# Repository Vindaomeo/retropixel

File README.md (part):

# retropixel

RGB matrix on a microcontroller, driven by the PC over USB-CDC with a
lean binary protocol (start token, length, data, CRC-16).

The controller is not just a dumb receiver: after reset it announces itself
once per second with a `READY` token that carries its display geometry.
So the PC doesn't need to know anything about the hardware — it asks.

```
┌──────────────┐      USB-CDC        ┌─────────────────┐   WS2812B
│  PC (Python) │ ◄─────────────────► │  Nano / Pico    │ ──────────► Panel(s)
│  script/     │   MX8 protocol      │  FW/ (FastLED)  │   1…4 data pins
└──────────────┘                     └─────────────────┘
```

Two setups are configured; switching between them takes **one line** in
`FW/mx8_config.h`:

| `MX_BOARD` | Area | Panels | Data pins |
|---|---|---|---|
| `MX_BOARD_8X8` | 8×8 = 64 LEDs | one 8×8 board | D6 |
| `MX_BOARD_16X32` | 32×16 = 512 LEDs | two 8×32 stacked | GP14 and GP17 |

> How a store-bought "8×32" panel is wired internally isn't in any
> datasheet. These ones run **column-wise in a serpentine (zigzag)**: eight pixels
> down the column, the next one back up. `script/mapcheck.py` measures that
> in thirty seconds — a lot faster than guessing.

The host notices none of the difference: it gets the dimensions via `READY` and
sends one contiguous area. How that breaks down into tiles and strands
only the firmware knows.

---

## Behavior after power-on

| State           | Display                      | Serial output        | Left via                                            |
|-----------------|------------------------------|----------------------|-----------------------------------------------------|
| **BOOT** (5 s)  | black                        | `READY` every second | valid `FRAME` → RUNNING · 5 s → TEST                |
| **TESTPATTERN** | 4 demos, switching every 6 s | `READY` every second | valid `FRAME` → RUNNING                             |
| **RUNNING**     | whatever the PC sends        | only `ACK`/`NACK`    | `RELEASE` → TEST · **1 min without a frame → DARK** |
| **DARK**        | black                        | `READY` every second | valid `FRAME` → RUNNING                             |

In practice: plug in the panel → 5 s of black with "I'm ready" calls →
then the demo runs, and the ready calls keep going. As soon as a Python script
sends the first frame, the PC takes over.

**If the PC drops out after that, the display goes black after 1 minute** — and
stays that way. Deliberately not back to the demo: as long as no PC has ever
shown up, the demo is the sensible sign of life; once a PC has been in control,
its silence is a fault, and a demo springing back to life would look
like normal operation. A valid `FRAME` brings the display back immediately.

The minute lives as `MX_PC_TIMEOUT_MS` in `FW/mx8_config.h`. `RELEASE` is
exempt from it — the orderly "I'm done" still leads back to the demo.

`PING` and `HELLO` deliberately trigger **no** mode change: the PC may
knock without killing the demo.

---

## Layout

```
retropixel/
├── FW/                          Arduino sketch
│   ├── FW.ino                   main program, state machine, test pattern
│   ├── mx8_config.h             ← adjust HERE: chipset, pins, geometry
│   ├── mx8_protocol.h           framing constants + CRC-16
│   ├── mx8_rx.h                 RX state machine (hardware-free, testable)
│   └── mx8_map.h                tile mapping (x,y) → chain index, testable
├── script/                      Python host
│   ├── hello_rainbow.py         scrolling text in rainbow colors
│   ├── smiley.py                smiley animation with smooth transitions
│   ├── speedtest.py             latency, throughput and flood measurement
│   ├── mapcheck.py              measure panel wiring → config block
│   ├── pixelwalk.py             every pixel individually, one per second
│   ├── rainbow.py               rainbow across the whole area, 6 patterns
│   ├── mx8_cli.py               command line (ports/monitor/demo/image/preview)
│   ├── mx8/protocol.py          framing/CRC — mirror of mx8_protocol.h
│   ├── mx8/mapping.py           pixel mapping — mirror of mx8_map.h
│   ├── mx8/link.py              serial connection, READY handshake, ACK flow
│   ├── mx8/framebuffer.py       RGB buffer + ANSI terminal preview
│   ├── mx8/font5x7.py           5×7 font as ASCII art, ASCII + umlauts
│   └── mx8/patterns.py          host animations
├── tests/                       cross-test C ↔ Python, no hardware needed
├── tools/build_check.sh         build firmware against real FastLED
├── docs/wiring.md               wiring diagram with graphics
├── docs/pixelgrid.md            pixel grid for square pixels (16×16 build)
├── docs/rainbow.gif             the six rainbow patterns
├── PROTOCOL.md                  complete protocol specification
├── WIRING.md                    wiring, power budget, pitfalls
└── README.md
```

---

## Hardware

| | |
|---|---|
| Board | Arduino Nano / Nano Every (AVR), **Raspberry Pi Pico** (RP2040) or **Pico 2 / 2 W** (RP2350) |
| Panel | WS2812B / NeoPixel-compatible, one or more modules |
| Data | one pin per panel → DIN, ideally with 330 Ω in series |
| Ground | GND controller **and** GND power supply **and** GND panel tied together |
| 5 V | see warning below |

From about 256 LEDs on, the **Pico** is clearly the better choice: native USB-CDC
has no baud rate limit, and FastLED clocks the LEDs out there via PIO+DMA in the
background instead of disabling interrupts. See
[PROTOCOL.md §6](PROTOCOL.md).

**→ Complete wiring diagram with power budget: [WIRING.md](WIRING.md)**
(graphical version: [`docs/wiring.md`](docs/wiring.md))

> **Power supply.** 64 WS2812B draw about **3.8 A** at full white. The
> Nano Every's 5V pin can't handle that — it hangs off USB and tops out at
> ~500 mA. Two clean options:
>
> 1. **External 5V power supply** to the panel, GND tied to the Nano. A
>    1000 µF electrolytic cap across the panel supply dampens the inrush current.
> 2. **Cap the brightness** (factory default): `MX_BRIGHTNESS_DEFAULT 40`
>    and `MX_MAX_MILLIAMPS 450` make FastLED automatically throttle down
>    far enough that USB power suffices.
>
> The default is deliberately option 2 — it should work right out of
> the box without you frying your USB port.

---

## Flashing the firmware

Required in the Arduino IDE:

* Board package **"Arduino megaAVR Boards"** (Tools → Board → Boards Manager)
* Library **FastLED ≥ 3.6** — older versions don't compile for the
  ATmega4809. Tested against 3.9.x.

Then open `FW/FW.ino` — in the IDE with `Ctrl+O` and the full path, or from
the shell:

```powershell
start FW\FW.ino          # Windows
```

The IDE loads the three headers automatically as additional tabs. Under *Tools*:
board **Arduino Nano Every**, Registers emulation **None (ATMEGA4809)** — then
upload.

> The sketch is deliberately called `FW.ino` and not `matrix8x8_nano_every.ino`: the
> Arduino IDE requires the folder name to match the name of the `.ino`.
> That way the sketch opens straight from the repo, without copying it into the
> sketchbook or creating a junction — and that holds on every machine
> that clones the repo.

### Different panel / different LED type

Everything you need is in `FW/mx8_config.h` — one line selects the setup:

```c
#define MX_BOARD  MX_BOARD_16X32   // or MX_BOARD_8X8
```

The chipset applies to both:

```c
#define LED_CHIPSET      WS2812B   // SK6812, WS2811, APA102, WS2801, LPD8806 …
#define LED_COLOR_ORDER  GRB       // RGB, BGR, … depending on the panel
// #define LED_CLOCK_PIN 7         // only for clocked chips (APA102 & co.)
```

The area is described as **tiles**. A single panel is the
special case 1×1:

```c
#define MX_TILE_W                32   // size of ONE tile (= one panel)
#define MX_TILE_H                8
#define MX_TILES_X               1    // tiles side by side
#define MX_TILES_Y               2    //       stacked vertically

#define MX_TILE_VERTICAL         1    // 0 = chain row-wise, 1 = column-wise
#define MX_TILE_SERPENTINE       1    // 1 = every other row/column reversed
#define MX_TILE_ORIGIN           0    // 0=top-left 1=t-r 2=b-l 3=b-r
#define MX_TILE_FLIP_ALT_ROWS    0    // 1 = every other tile row rotated 180°
#define MX_TILE_ORDER_SERPENTINE 0    // tiles chained in a serpentine

#define MX_STRANDS               2    // data pins
#define LED_DATA_PIN             14   // tile 0  (Pico GP14)
#define LED_DATA_PIN_2           17   // tile 1  (Pico GP17)
```

The host has to change **nothing**: the geometry comes along in the `READY` token,
and the wire format is always plain RGB, row-major, top-left first.
Reordering and tile mapping are the firmware's job.

### Don't guess the wiring — measure it

How a store-bought panel is soldered internally is rarely in the datasheet. Instead
of trying all eight combinations:

```bash
python script/mapcheck.py -p COM4 --tile 32x8 --tiles 1x2 --strands 2
```

The script uses `CMD_RAW` and so writes **without** mapping straight into the
LED chain — whatever lights up is the physical wiring. Four questions later
the finished config block is on screen, and a test image (red dot
top left, green border, tile numbers) shows beforehand whether it's right.
The PC does the mapping math here, so **nothing needs flashing** to
test a hypothesis.

```bash
python script/mapcheck.py --chase        # just run along the chain
python script/mapcheck.py --verify 16x32 # test image with a known preset
```

**Typical failure patterns:**

| Symptom | Cause |
|---|---|
| Red and green swapped | `LED_COLOR_ORDER` — swap `GRB` ↔ `RGB` |
| Dot moves in a **snake line**, every other row mirrored | toggle `MX_TILE_SERPENTINE` (0 ↔ 1) |
| Dot moves **vertically** instead of horizontally | The chain is column-wise: `MX_TILE_VERTICAL 1` |
| Dot only travels **8 pixels**, then jumps | Run length = tile height with a vertical chain. Usually `MX_TILE_VERTICAL 1` + `MX_TILE_SERPENTINE 1` |
| Image rotated by 90° | toggle `MX_TILE_VERTICAL` |
| Image upside down / mirrored | try the `MX_TILE_ORIGIN` values |
| Top half correct, bottom half rotated | `MX_TILE_FLIP_ALT_ROWS` to `1` |
| Bottom half stays dark | second data pin, `MX_STRANDS`, its own 5 V |
| First LED flickers, rest OK | signal level problem: 330 Ω in the data line, shorter cable |

### Two panels as one display area

Each panel gets its **own data pin**. FastLED then clocks them out
simultaneously — `show()` for 512 LEDs takes 7.98 ms instead of 15.66 ms:

```c
FastLED.addLeds<WS2812B, 14, GRB>(leds,   0, 256);   // top panel    (tile 0)
FastLED.addLeds<WS2812B, 17, GRB>(leds, 256, 256);   // bottom panel (tile 1)
```

`FW.ino` does this automatically based on `MX_STRANDS`; up to four strands
are wired up (`LED_DATA_PIN_3`, `LED_DATA_PIN_4`). The strand boundary must fall on
a tile boundary — `mx8_config.h` checks that at compile time.

> **512 WS2812B draw 30.7 A at full white.** That's no longer a USB issue,
> it's a power supply issue. `MX_MAX_MILLIAMPS` is set to 2000 mA for this
> setup; FastLED automatically throttles the brightness far enough that the
> limit is respected. Feed power into both panels at the same point, don't
> daisy-chain it.

### Raspberry Pi Pico

Same firmware, no changes needed — `FASTLED_ALLOW_INTERRUPTS` is now only
set on AVR, because the RP2040 has to keep interrupts enabled (otherwise USB-CDC
dies). In the Arduino IDE:

* Board package **"Raspberry Pi Pico/RP2040"** by *earlephilhower*
* Board *Raspberry Pi Pico*, USB Stack *Pico SDK*
* `MX_SERIAL_BAUD` has no effect on the Pico: native USB-CDC always runs at
  full speed, no matter what baud rate host and firmware report.

On the RP2040, FastLED uses the PIO driver with DMA out of the box
(`FASTLED_RP2040_CLOCKLESS_PIO` defaults to `1`, up to 8 strands
in parallel). So clocking out runs in the background while the next
frame is already coming in.

---

## Python side

```bash
cd script
pip install pyserial          # required
pip install pillow            # optional, only for image/GIF mode
```

### Setting port and baud rate

For **every** script the port comes via `-p`, the baud rate via `-b`:

```powershell
python hello_rainbow.py -p COM4
python speedtest.py -p COM4
python mx8_cli.py demo -p COM4 --pattern plasma
```

If you don't want to type that every time, set it once per console session:

```powershell
$env:MX8_PORT = "COM4"          # PowerShell
```
```bash
export MX8_PORT=/dev/ttyUSB0    # Linux/macOS
```

Precedence: `-p` beats `MX8_PORT`, which beats auto-detection. Likewise
`-b` / `MX8_BAUD` / 115200. `python mx8_cli.py ports` lists what's there.

> **The baud rate has to be the same on both sides** — but the host will find it
> on its own if need be. If no `READY` arrives at the configured value, it tries
> `1000000 → 500000 → 250000 → 115200` in turn and reports the switch in the log.
> An explicit `-b` or `MX8_BAUD` turns the search off.
>
> On the firmware side the rate per setup is in `FW/mx8_config.h`: the 8×8 at
> 115200, the 16×32 setup at **1000000**.

#### On the Pico a higher baud rate buys you nothing

That's not penny-pinching in the wrong place, it's physics: the Pico has
**native USB-CDC**. The "baud rate" there is just a number that host and device
report to each other and both ignore — the transfer runs at USB Full Speed
(12 Mbit/s). 1543 B per frame are gone in just over 1 ms.

The bottleneck is the **WS2812B protocol**: 800 kHz, 24 bits per LED = 30 µs
per LED. For 256 LEDs per strand that's 7.98 ms → **125 fps**, no matter what's in
`MX_SERIAL_BAUD`. The only way to go faster is more data pins (`MX_STRANDS 4`
would reach ~250 fps) or clocked chips like the APA102.

On a UART board (Nano, Nano Every), on the other hand, the value really matters —
there the difference between 115200 and 500000 is a factor of 4.

### Classic Arduino Nano instead of Nano Every

Works just the same, two things are different:

* **Board in the IDE:** *Arduino Nano*, processor *ATmega328P*. If the upload
  aborts with `avrdude: stk500_recv(): programmer is not responding`, it's
  a clone with the old bootloader → processor *ATmega328P (Old Bootloader)*.
* **Port detection:** classic Nanos sit behind a CH340 or FTDI, not
  an Arduino USB ID. Auto-detection does know these converters, but can't
  tell them apart from other USB-serial devices — if several are
  plugged in, you have to pick one with `-p COM4`.

The ATmega328P has 2 KB of RAM. Measured on the fully linked binary (see
[Building without the Arduino IDE](#building-without-the-arduino-ide)), with FastLED
3.10.5: **1006 B RAM, 18434 B flash** — 49 % and 56 %. It fits, but there's not much headroom:
a 16×16 panel alone would need 768 B of framebuffer plus 776 B of receive buffer
and would no longer work on this chip.

**If `speedtest.py` shows a constant latency of ~16 ms:** that's not
your code, it's the FTDI driver's *Latency Timer*, which defaults to 16 ms
and collects small packets instead of sending them right away. Fix it in
Device Manager → Ports (COM & LPT) → COM4 → Properties → Port Settings →
Advanced → **Latency Timer to 1 ms**. The frame rate goes up noticeably afterwards.

### The test programs

```bash
python hello_rainbow.py                    # "Hello World" as scrolling text, rainbow
python hello_rainbow.py --preview          # the same in the terminal, no hardware
python hello_rainbow.py --text "Grüße!" --speed 12 --loops 3

python smiley.py                           # neutral → sad → happy → wink
python smiley.py --preview --hold 2 --morph 1
python smiley.py --winks 1 --loops 3

python speedtest.py                        # measure latency + throughput
python speedtest.py --flood                # plus the stress test without ACK
python speedtest.py --preview              # just the baud rate math

python pixelwalk.py                        # 1st pass fast (video), then 1 pixel/s
python pixelwalk.py --interval 0.1 --trail # fast afterwards too, with afterglow
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
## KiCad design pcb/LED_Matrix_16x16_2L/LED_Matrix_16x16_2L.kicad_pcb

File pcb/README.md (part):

# WS2812B-Matrix 16x16 (10 mm Raster), generiert

## Inhalt

- `gen_ledmatrix.py`: Generator (reines Python 3.8+, keine Abhängigkeiten)
- `LED_Matrix_16x16/`: fertiges KiCad-Projekt (Schaltplan + 4-Lagen-Layout, Zonen gefüllt)

- `LED_Matrix_16x16_2L/`: dieselbe Matrix als 2-Lagen-Platine

## Neu generieren

```
python gen_ledmatrix.py                  (4 Lagen -> LED_Matrix_16x16)
python gen_ledmatrix.py --layers 2       (2 Lagen -> LED_Matrix_16x16_2L)
```

## 2-Lagen-Variante

| Lage | Inhalt |
|------|--------|
| F.Cu | LEDs, Kondensatoren, Datenleitung, +5V-Fläche um alles herum |
| B.Cu | GND-Fläche, Einspeise-Pads, Pegelwandler, Daten-Pads |

- Schaltplan, Platzierung, Stege, Löcher und Datenführung sind identisch mit der 4-Lagen-Version.
- VDD jeder LED hängt direkt an der +5V-Fläche oben. Die Fläche läuft unter jedem LED-Körper durch und ist damit überall zusammenhängend.
- GND-Pads der LEDs und Kondensatoren gehen per Via auf die GND-Fläche unten.
- Die +5V-Einspeise-Pads (unten) haben je 6 Vias zur +5V-Fläche oben.
- Die +5V-Fläche oben ist von den Datenleitungen durchlöchert und leitet schlechter als eine volle Innenlage. Daher: 2 oz Kupfer bestellen, wenn es das Budget erlaubt, und alle 4 Einspeisepaare anschließen.
- DRC: 0 Fehler, 0 ungeroutete Verbindungen. Netzliste Schaltplan ↔ Layout: alle 1557 Pins identisch.

Parameter stehen oben im Script (Rastermaß, Stegbreite, Löcher, Einspeisepunkte, Leiterbahnbreiten).
Achtung: Der Generator überschreibt das Projekt komplett. Manuelle Änderungen in KiCad also erst machen, wenn die Parameter passen.

## Öffnen in KiCad 8

Die Dateien sind im KiCad-7-Format geschrieben. KiCad 8 öffnet sie direkt und speichert sie beim ersten Speichern im 8er-Format.
Danach im PCB-Editor einmal **Zonen füllen (B)** und **DRC** laufen lassen.

## Aufbau

| Lage   | Inhalt |
|--------|--------|
| F.Cu   | 256 × WS2812B (5050), 256 × 100 nF (0402), Datenleitung als Serpentine |
| In1.Cu | GND-Fläche |
| In2.Cu | +5V-Fläche |
| B.Cu   | GND-Fläche, Einspeise-Pads, Pegelwandler, Daten-Pads |

- **Platine:** 160 × 160 mm, Zelle 10 × 10 mm
- **Trennstege:** 1,2 mm breite Streifen auf allen Zellgrenzen sind bauteilfrei (Rule Areas "Steg_*", Footprints verboten, Leiterbahnen erlaubt). Die Stege sind auf Dwgs.User eingezeichnet.
  Lichte Weite pro Zelle: 8,8 mm. LED-Courtyard: 6,9 × 5,5 mm.
- **Löcher:** 9 × Ø2,2 mm (NPTH) an den Steg-Kreuzungen 4/8/12, für M2-Schrauben oder Zapfen des Gitters.
- **Fiducials:** 3 Passermarken auf der Oberseite an den Steg-Kreuzungen (5,2), (14,2) und (2,11), unsymmetrisch angeordnet. 1 mm Kupferpunkt, 2 mm Maskenöffnung, 3 mm kupferfrei. Sie liegen unter dem Trenngitter, das erst nach der Bestückung aufgesetzt wird.
- **Fiducials Unterseite:** 3 weitere an denselben Kreuzungen auf B.Cu (FID4-FID6), damit auch die Unterseite maschinell bestückt werden kann (`JLC_BOTTOM = True`).
- **Datenkette:** D1 links oben, Zeile 1 nach rechts, Zeile 2 nach links usw. (Serpentine). D256 endet links unten.
- **Eingang (Unterseite, unter D1):** Pad DIN → 74AHCT1G125 (3,3 V → 5 V) → 33 Ω → D1. Daneben ein GND-Pad fürs Datenkabel.
- **Ausgang (Unterseite, unter D256):** Pad DOUT + GND, zum Weiterverketten.
- **Einspeisung (Unterseite):** 4 Paare Lötpads (+5V / GND, je 3,6 × 5 mm mit 6 Vias). Bei voller Helligkeit fließen bis ca. 15 A, also möglichst alle 4 Paare anschließen.

## Prüfung

- DRC: 0 Fehler, 0 ungeroutete Verbindungen
- Netzliste Schaltplan ↔ Layout: alle 1557 Pins identisch

## Hinweise für die Fertigung

- Innenlagen mit 1 oz Kupfer bestellen, wenn möglich (bessere Stromverteilung).
- Die Bauteile auf der Unterseite (U1, R1, C257, Pads) lassen sich gut von Hand löten; die Oberseite ist für die Bestückung durch den Fertiger gedacht.
- Software-Mapping: Serpentine (jede zweite Zeile umgekehrt), in FastLED/WLED als "serpentine" einstellbar.
- Einen Elko (z.B. 1000 µF) direkt am Netzteil bzw. an der Einspeisung vorsehen.

## JLCPCB-Fertigung und Bestückung

Jedes Bauteil hat ein Feld **LCSC** mit der JLC/LCSC-Teilenummer, im Schaltplan und im Layout. Damit funktionieren auch die KiCad-Plugins "Fabrication Toolkit" und "JLCPCB Tools", falls du sie später nutzen willst.

| Bauteil | Wert | Footprint | LCSC |
|---|---|---|---|
| D1-D256 | WS2812B-B/W | LED_WS2812B_PLCC4_5.0x5.0mm | C2843785 (dein Eintrag; Alternativen C2761795, C114586) |
| C1-C257 | 100 nF X7R | 0402 | C1525 (Basic) |
| R1 | 33 Ω | 0402 | C25105 (Basic) |
| U1 | SN74AHCT1G125DBVR | SOT-23-5 | C7484 |

Im Ordner `jlcpcb/` jedes Projekts liegen fertige Upload-Dateien:

- `*_Gerber.zip`: Gerber + Bohrdaten (beim PCB-Bestellen hochladen)
- `*_BOM.csv`: Stückliste (Comment, Designator, Footprint, LCSC Part #)
- `*_CPL.csv`: Bestückungsdaten (Position in mm ab linker unterer Ecke, Drehwinkel schon für JLC korrigiert: WS2812B und SOT-23 +180°)
- `Handbestueckung.txt`: Bauteile, die JLC nicht bestückt

**Standard:** JLC bestückt nur die Oberseite (256 LEDs + 256 Kondensatoren). U1, R1 und C257 auf der Unterseite lötest du selbst, das spart den Aufpreis für beidseitige Bestückung. Mit `JLC_BOTTOM = True` im Script kommen sie mit in BOM/CPL.

**Bestellablauf:** Gerber-Zip hochladen → Lagen/Kupferstärke wählen → "PCB Assembly" aktivieren, Seite "Top" → BOM und CPL hochladen → in der Vorschau die LED-Ausrichtung prüfen (Pin-1-Markierung) → Lagerbestand der Teile prüfen.

Nach Änderungen in KiCad die Gerber neu erzeugen: Datei → Fertigungsunterlagen → Gerber + Bohrdateien, oder mit dem Plugin "Fabrication Toolkit" (erzeugt Gerber, BOM und CPL in einem Schritt aus dem LCSC-Feld).

## Lichtgitter (3D-Druck)

`gen_lightgrid.py` erzeugt das Trenngitter als STL, passend zur Platine. Raster, Stegbreite, Matrixgröße und Bohrungen liest es direkt aus `gen_ledmatrix.py`, beide Dateien müssen also im selben Ordner liegen.

```
pip install manifold3d numpy
python gen_lightgrid.py          -> LED_Matrix_16x16_Lichtgitter.stl
python gen_lightgrid.py --test   -> Teststück 3 × 3 Zellen (--test 4 für 4 × 4)
```

- 160 × 160 × 10 mm, Stege 1,2 mm genau auf den bauteilfreien Streifen der Platine, Außenrahmen 1,2 mm innerhalb der Platinenkante
- Befestigung: eingestellt ist `FIX = "peg"` (dein Eintrag): 9 Zapfen Ø 1,95 mm durch die inneren Bohrungen, ragen unten 0,6 mm heraus zum Verkleben oder Verschmelzen. Die STL ist dafür umgedreht (Oberseite aufs Druckbett). `"screw"` (Schraubdome Ø 4 mm) wäre in den Pixeln sichtbar
- Engster Abstand Gitter zu einem Bauteil-Courtyard: 0,35 mm (Randspalten), innen 0,95 mm
- Druck: Auflageseite nach unten, ohne Stützen. 0,4-mm-Düse, weißes oder schwarzes PLA (weiß reflektiert mehr Licht, schwarz trennt die Pixel schärfer)

Parameter oben im Script: `HEIGHT` (Höhe), `FIX` ("screw", "peg" = Zapfen durch die Bohrungen, "none"), `OUTER_T` (für lückenlos aneinandergereihte Panels `pcb.WALL / 2`), `TOP_CHAMFER` (Stege oben verjüngt, z.B. 0.6).

**Teststück:** Vor dem großen Druck ein 3 × 3-Stück (ca. 3 g, 30,6 × 30,6 mm) in den Farben drucken, die du vergleichen willst. Es passt in die Ecke links oben bei D1 (Rahmen links und oben, voller Steg rechts und unten). Dort einzelne LEDs voll aufdrehen und schauen, wie stark die Nachbarzellen mitleuchten.

## Trägerrahmen (Rückseite)

`gen_lightgrid.py` erzeugt neben dem Lichtgitter auch den Trägerrahmen (`*_Rahmen.stl`), gedacht zum Einbau in ein Gehäuse.

- Läuft auf der Rückseite 10 mm breit am Rand entlang (`FRAME_BAND` in `gen_ledmatrix.py`). Dieser Streifen ist auf der Platinenunterseite bauteilfrei, die Auflage ist auf B.Fab eingezeichnet.
- 10 mm Bautiefe (`FRAME_DEPTH`), 2 mm Außenwand, Auflage mit 45°-Schräge.
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
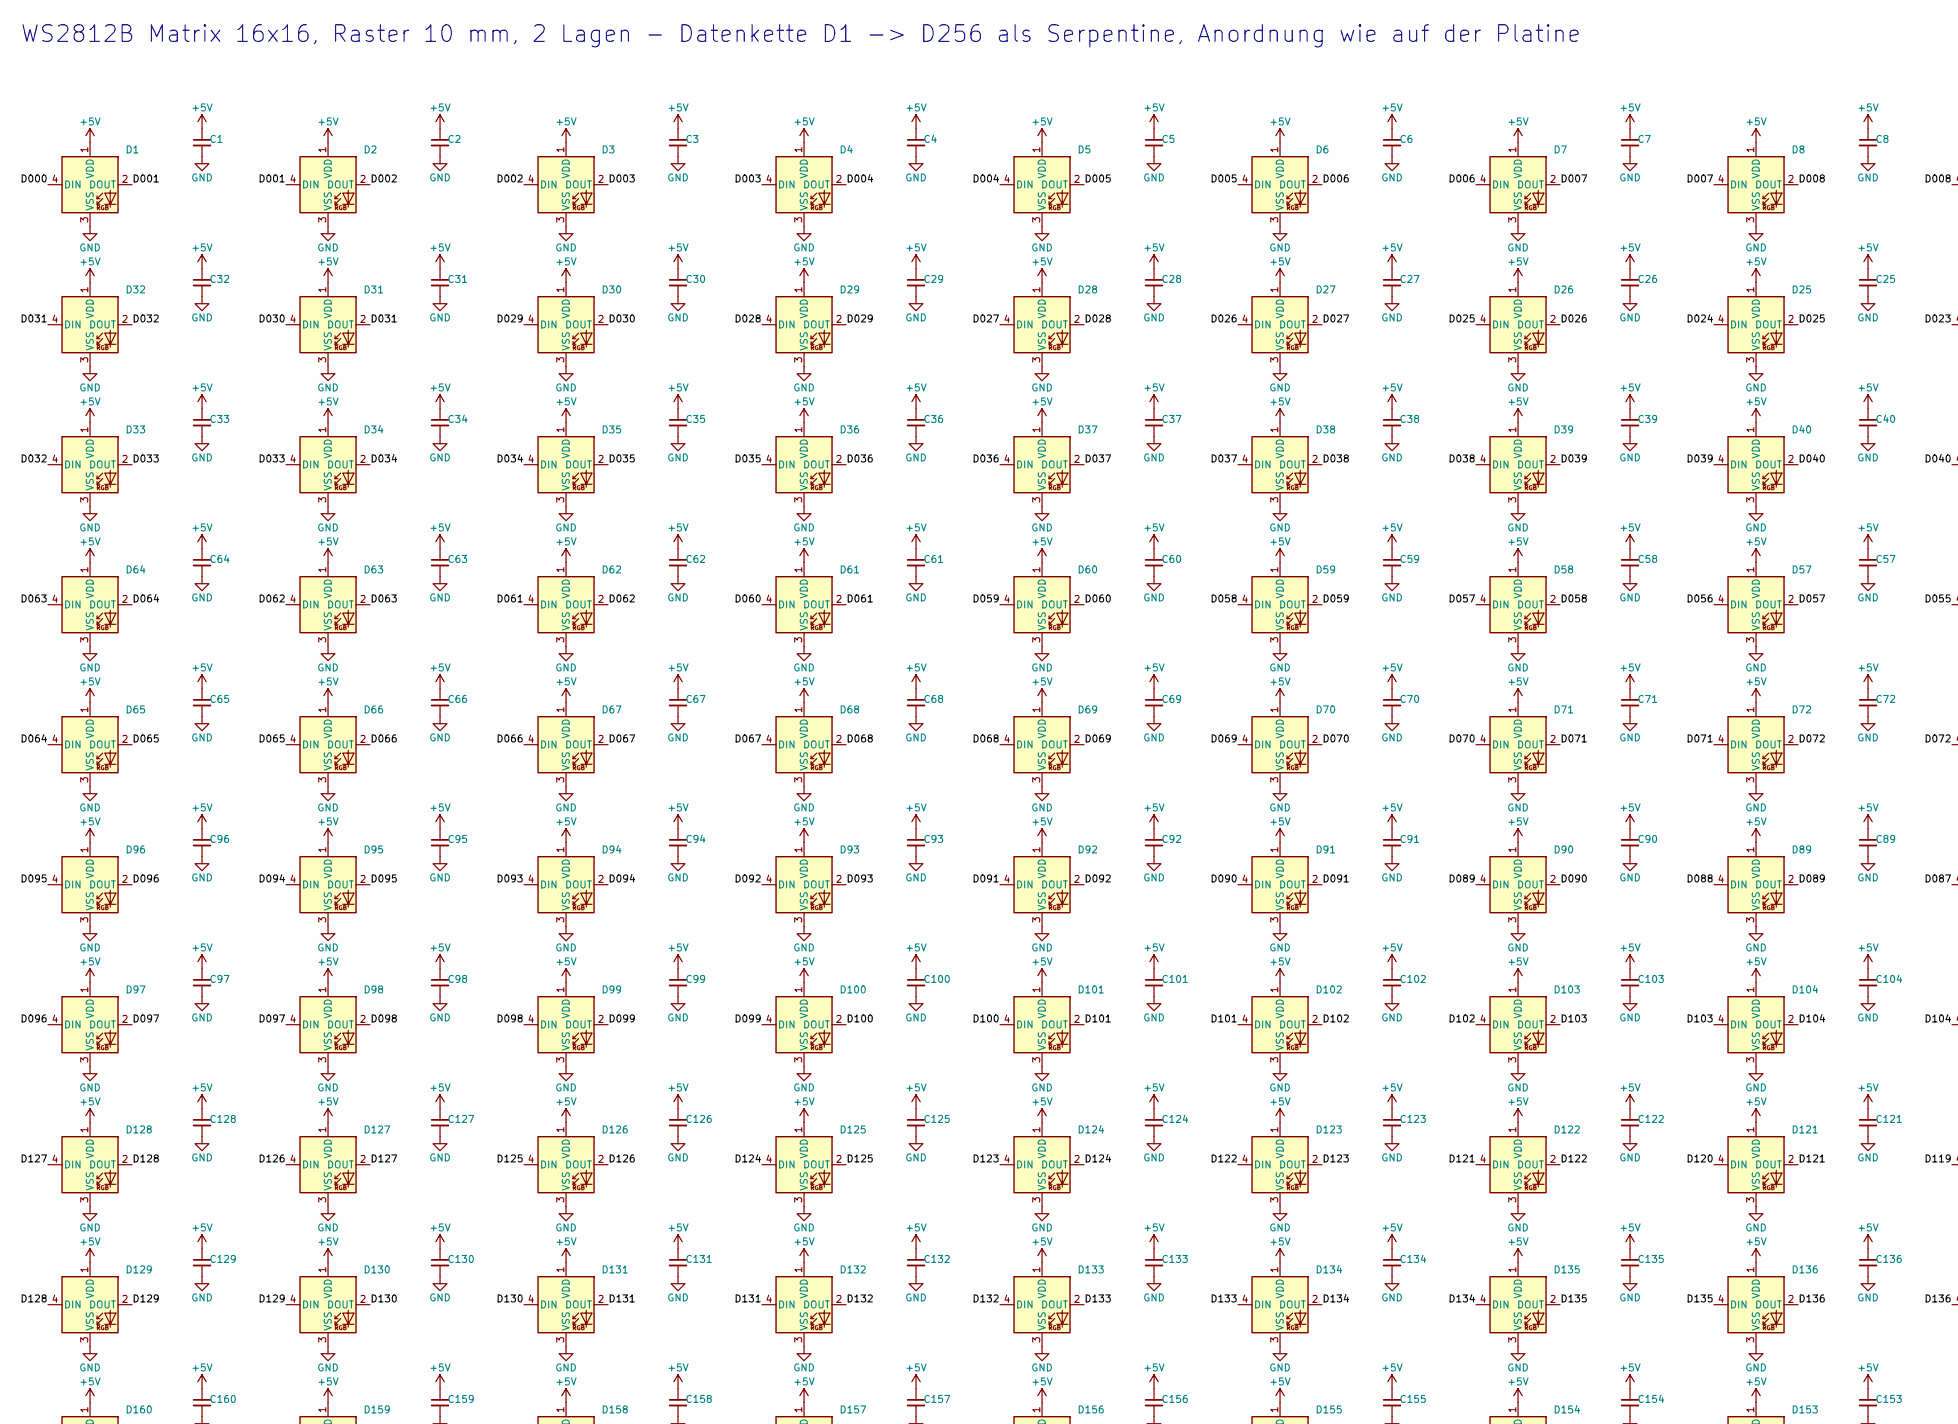
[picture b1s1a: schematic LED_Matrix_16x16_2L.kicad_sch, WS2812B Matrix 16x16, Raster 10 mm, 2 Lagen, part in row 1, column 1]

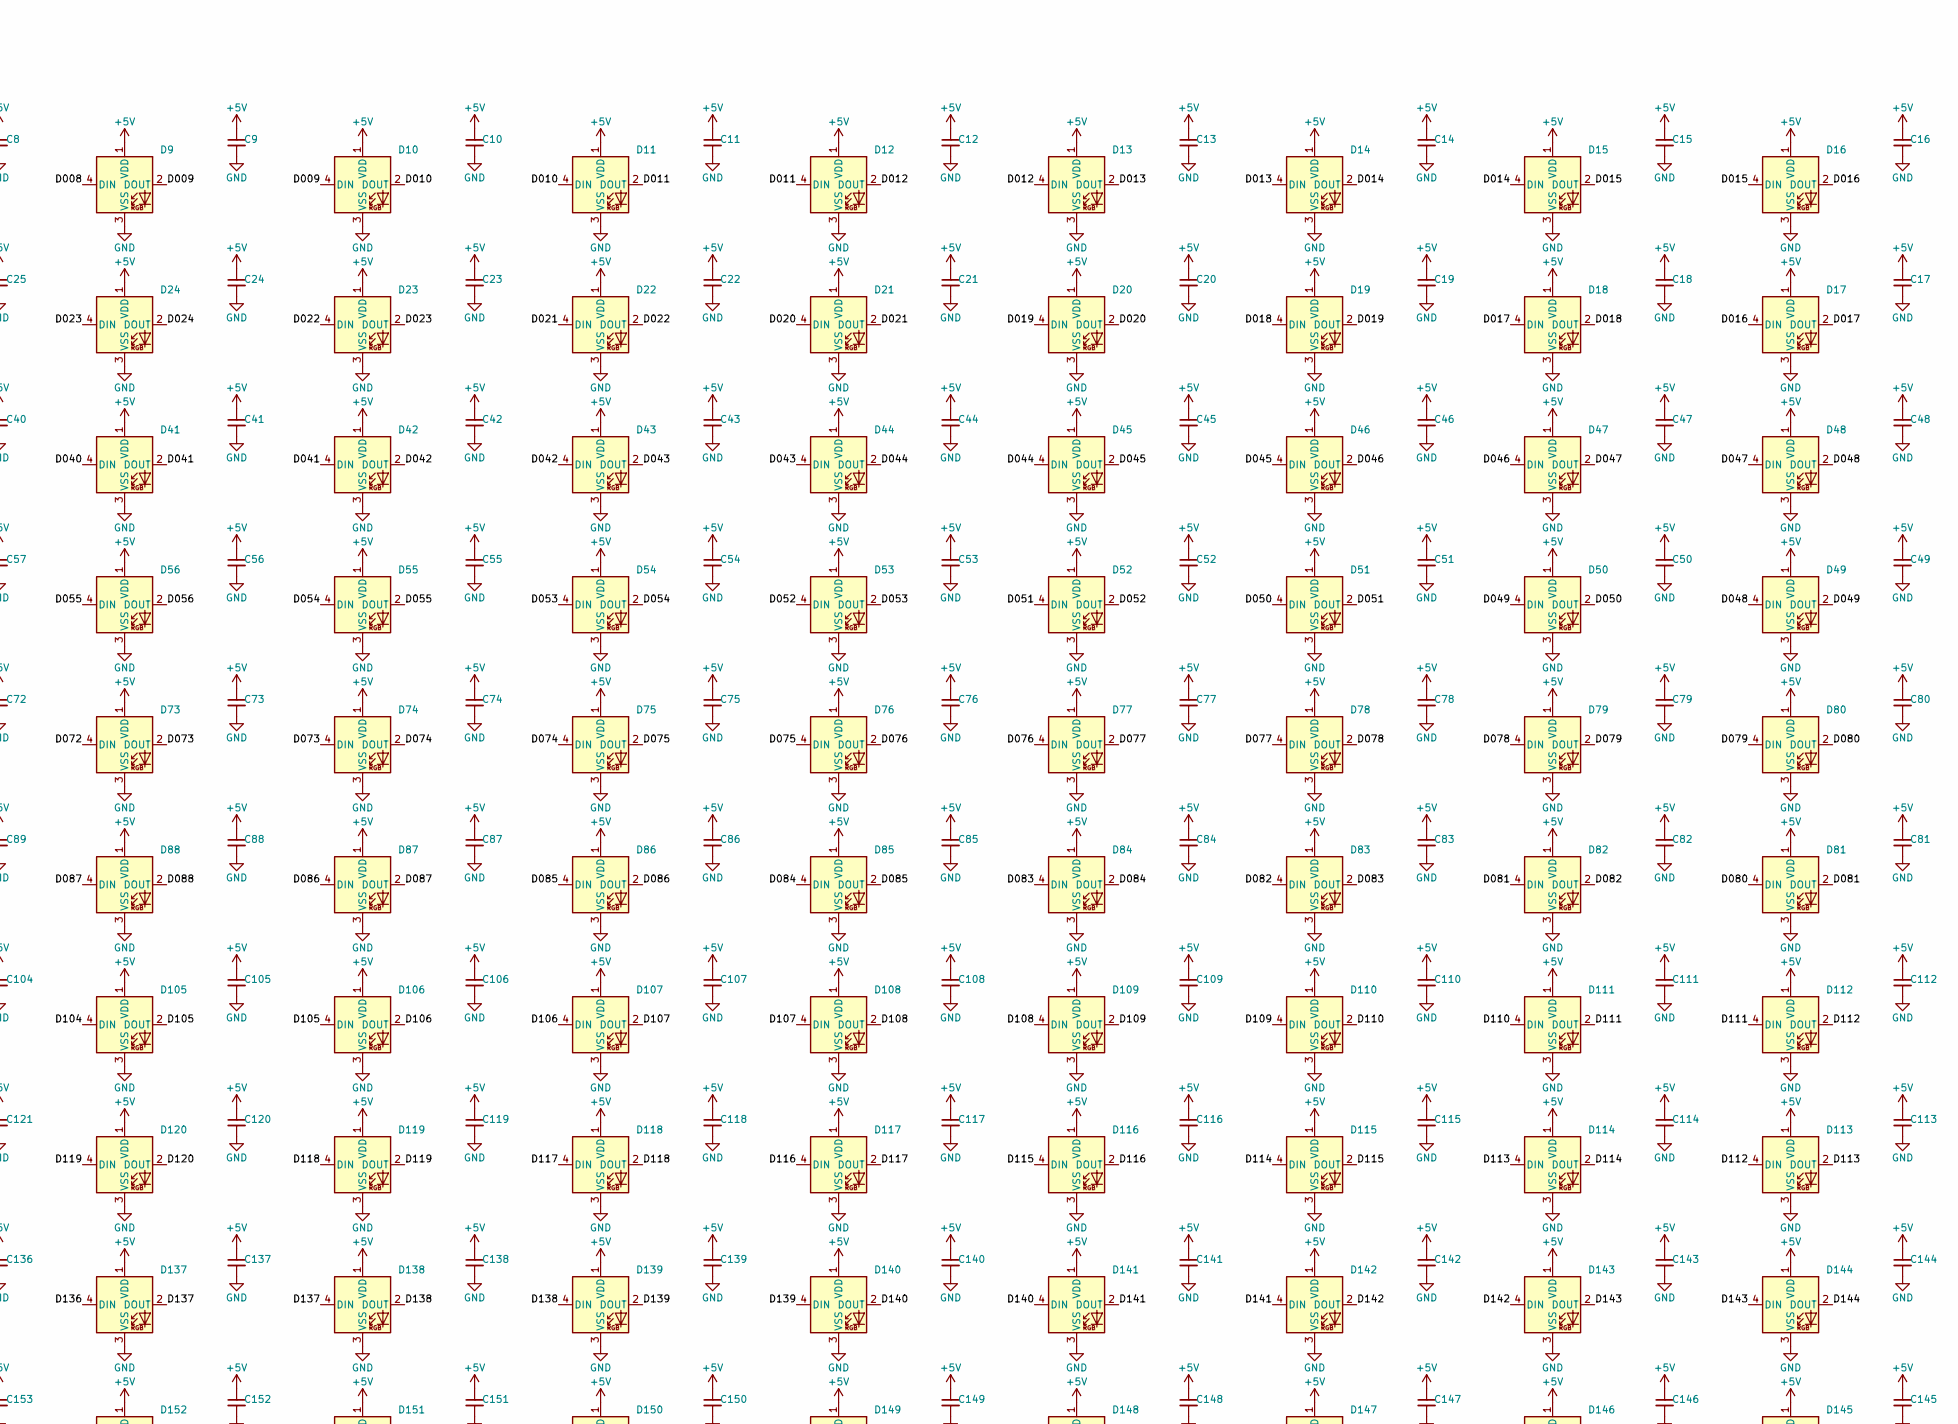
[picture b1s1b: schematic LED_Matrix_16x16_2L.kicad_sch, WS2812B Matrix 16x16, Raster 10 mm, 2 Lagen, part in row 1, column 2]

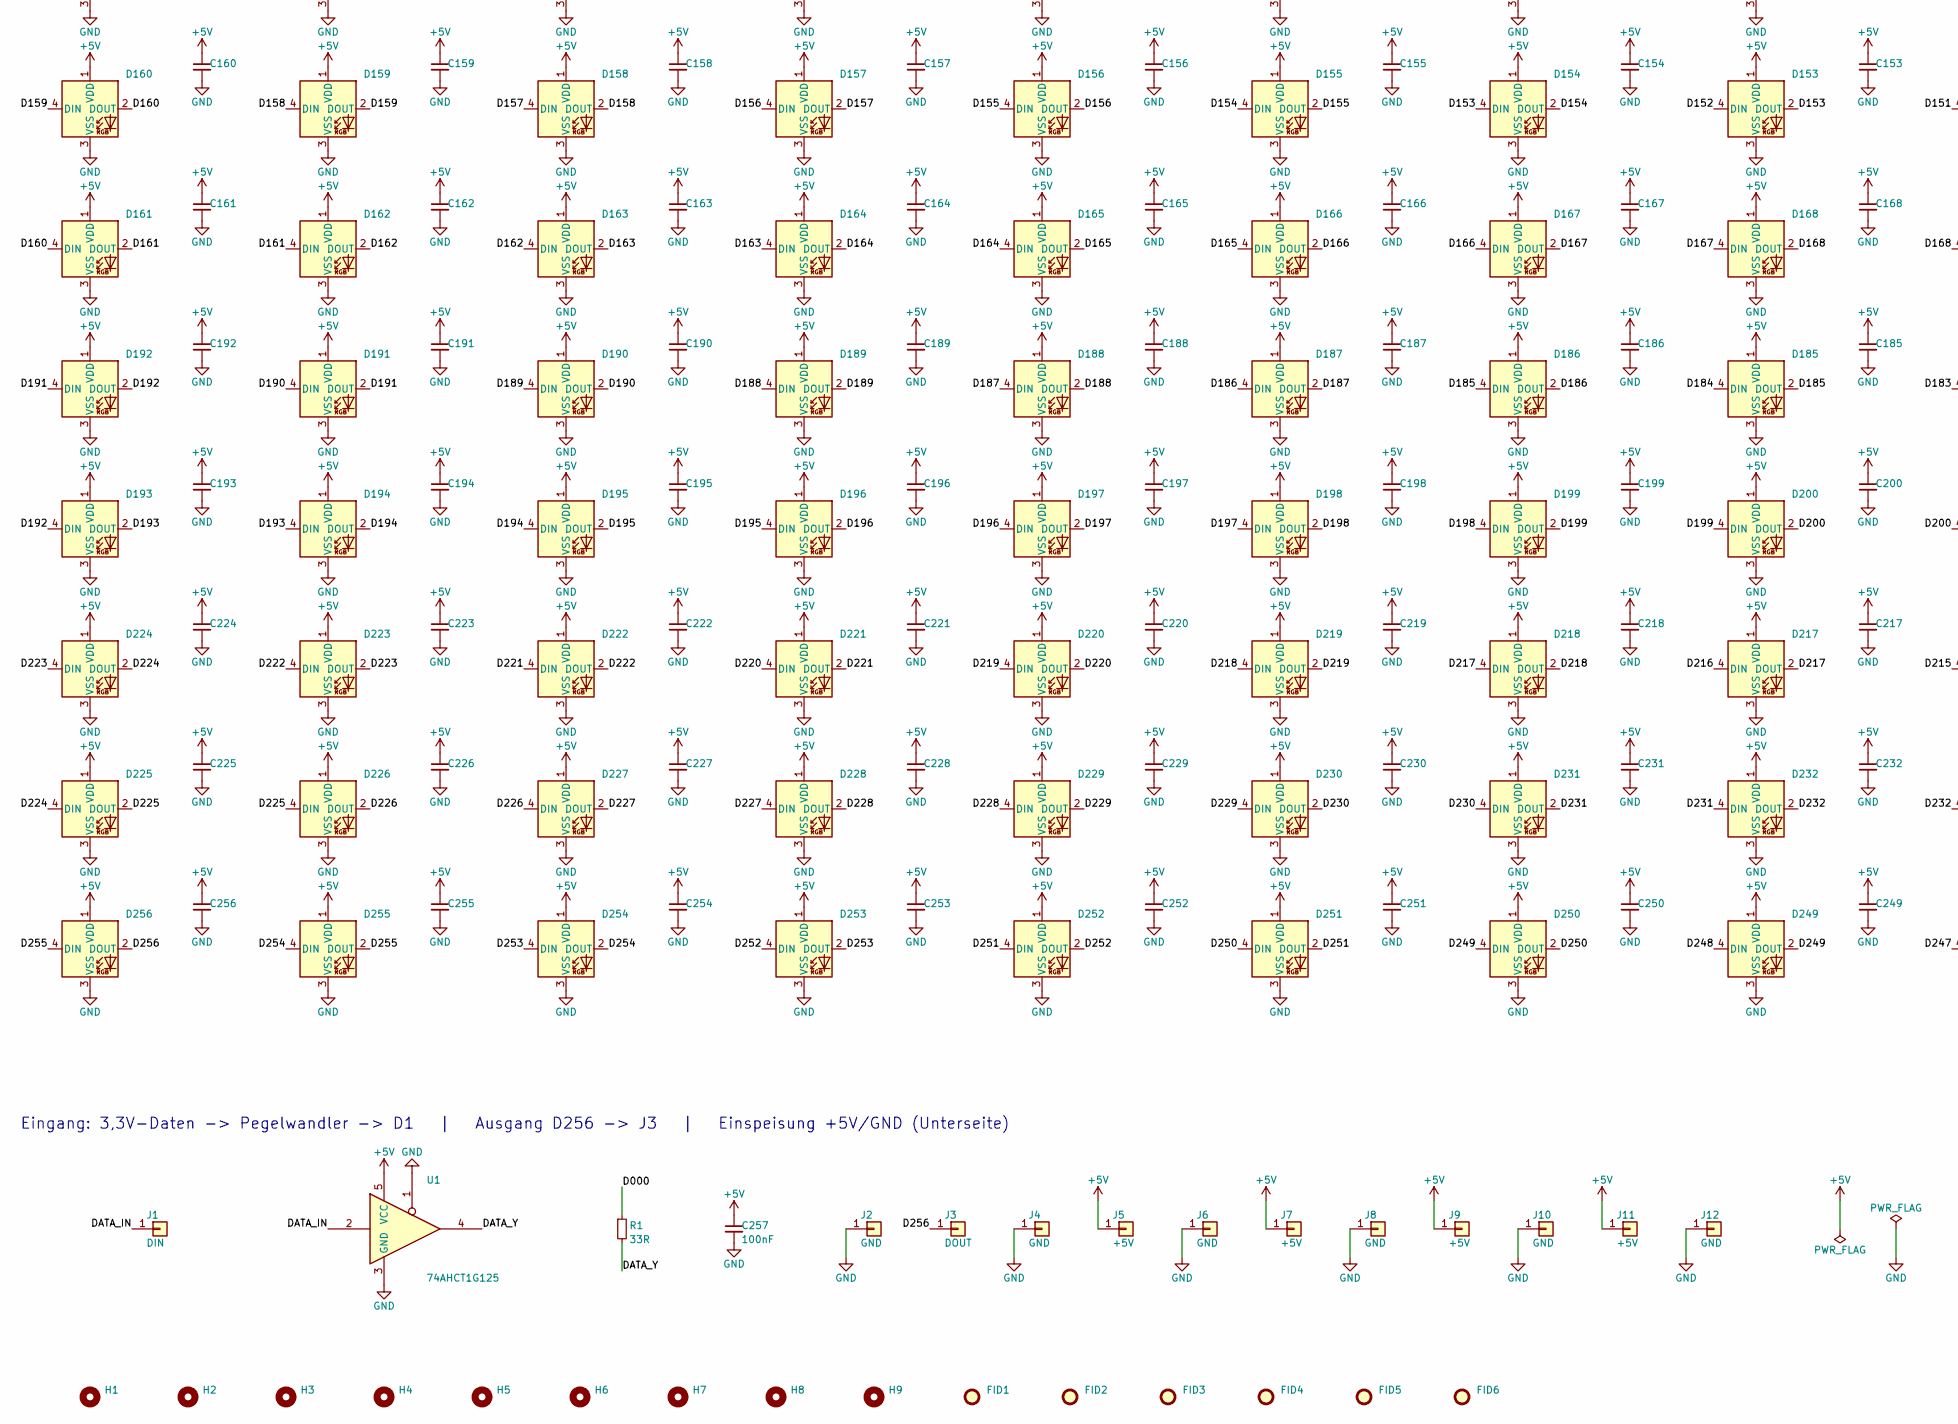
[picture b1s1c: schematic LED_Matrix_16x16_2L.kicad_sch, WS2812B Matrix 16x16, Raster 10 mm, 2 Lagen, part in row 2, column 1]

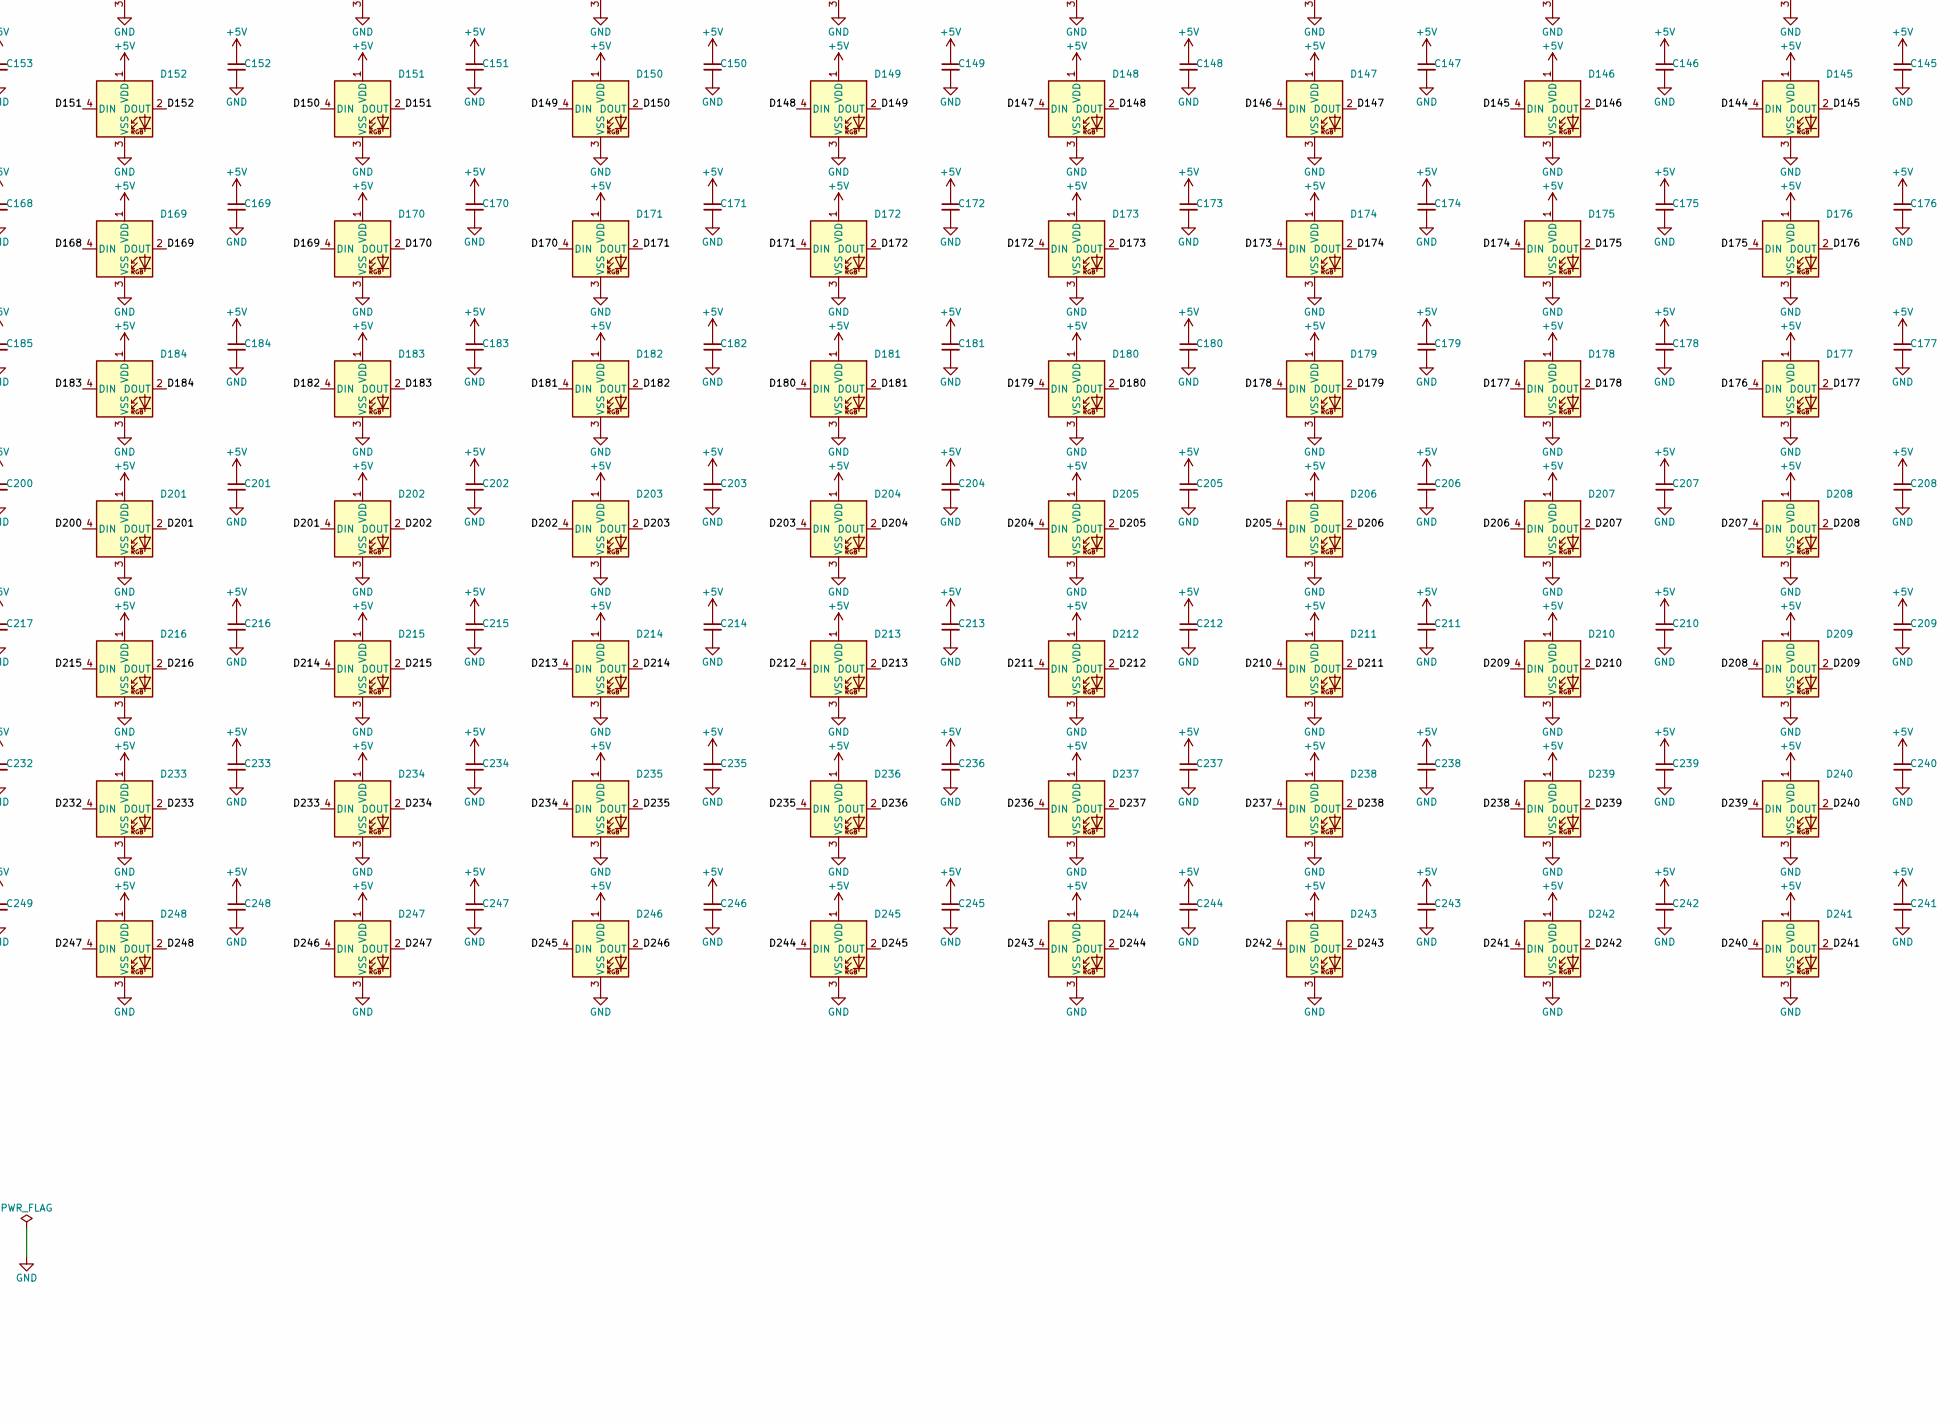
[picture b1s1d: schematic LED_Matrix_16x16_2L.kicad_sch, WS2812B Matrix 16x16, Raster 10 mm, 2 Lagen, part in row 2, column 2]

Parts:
C1, C2, C3, C4, C5, C6, C7, C8, C9, C10, C11, C12, C13, C14, C15, C16, C17, C18, C19, C20, C21, C22, C23, C24, C25, C26, C27, C28, C29, C30, C31, C32, C33, C34, C35, C36, C37, C38, C39, C40, C41, C42, C43, C44, C45, C46, C47, C48, C49, C50, C51, C52, C53, C54, C55, C56, C57, C58, C59, C60, C61, C62, C63, C64, C65, C66, C67, C68, C69, C70, C71, C72, C73, C74, C75, C76, C77, C78, C79, C80, C81, C82, C83, C84, C85, C86, C87, C88, C89, C90, C91, C92, C93, C94, C95, C96, C97, C98, C99, C100, C101, C102, C103, C104, C105, C106, C107, C108, C109, C110, C111, C112, C113, C114, C115, C116, C117, C118, C119, C120, C121, C122, C123, C124, C125, C126, C127, C128, C129, C130, C131, C132, C133, C134, C135, C136, C137, C138, C139, C140, C141, C142, C143, C144, C145, C146, C147, C148, C149, C150, C151, C152, C153, C154, C155, C156, C157, C158, C159, C160, C161, C162, C163, C164, C165, C166, C167, C168, C169, C170, C171, C172, C173, C174, C175, C176, C177, C178, C179, C180, C181, C182, C183, C184, C185, C186, C187, C188, C189, C190, C191, C192, C193, C194, C195, C196, C197, C198, C199, C200, C201, C202, C203, C204, C205, C206, C207, C208, C209, C210, C211, C212, C213, C214, C215, C216, C217, C218, C219, C220, C221, C222, C223, C224, C225, C226, C227, C228, C229, C230, C231, C232, C233, C234, C235, C236, C237, C238, C239, C240, C241, C242, C243, C244, C245, C246, C247, C248, C249, C250, C251, C252, C253, C254, C255, C256, C257: 100nF; C_0402_1005Metric; LCSC C1525
D1, D2, D3, D4, D5, D6, D7, D8, D9, D10, D11, D12, D13, D14, D15, D16, D17, D18, D19, D20, D21, D22, D23, D24, D25, D26, D27, D28, D29, D30, D31, D32, D33, D34, D35, D36, D37, D38, D39, D40, D41, D42, D43, D44, D45, D46, D47, D48, D49, D50, D51, D52, D53, D54, D55, D56, D57, D58, D59, D60, D61, D62, D63, D64, D65, D66, D67, D68, D69, D70, D71, D72, D73, D74, D75, D76, D77, D78, D79, D80, D81, D82, D83, D84, D85, D86, D87, D88, D89, D90, D91, D92, D93, D94, D95, D96, D97, D98, D99, D100, D101, D102, D103, D104, D105, D106, D107, D108, D109, D110, D111, D112, D113, D114, D115, D116, D117, D118, D119, D120, D121, D122, D123, D124, D125, D126, D127, D128, D129, D130, D131, D132, D133, D134, D135, D136, D137, D138, D139, D140, D141, D142, D143, D144, D145, D146, D147, D148, D149, D150, D151, D152, D153, D154, D155, D156, D157, D158, D159, D160, D161, D162, D163, D164, D165, D166, D167, D168, D169, D170, D171, D172, D173, D174, D175, D176, D177, D178, D179, D180, D181, D182, D183, D184, D185, D186, D187, D188, D189, D190, D191, D192, D193, D194, D195, D196, D197, D198, D199, D200, D201, D202, D203, D204, D205, D206, D207, D208, D209, D210, D211, D212, D213, D214, D215, D216, D217, D218, D219, D220, D221, D222, D223, D224, D225, D226, D227, D228, D229, D230, D231, D232, D233, D234, D235, D236, D237, D238, D239, D240, D241, D242, D243, D244, D245, D246, D247, D248, D249, D250, D251, D252, D253, D254, D255, D256: WS2812B; LED_WS2812B_PLCC4_5.0x5.0mm_P3.2mm; LCSC C2843785
FID1, FID2, FID3, FID4, FID5, FID6: Fiducial; Fiducial_1mm_Mask2mm
H1, H2, H3, H4, H5, H6, H7, H8, H9: Hole; NPTH_2.2mm
J1: DIN; SolderPad_3x2mm
J2, J4: GND; SolderPad_3x2mm
J3: DOUT; SolderPad_3x2mm
J5, J7, J9, J11: +5V; SolderPad_3.6x5mm
J6, J8, J10, J12: GND; SolderPad_3.6x5mm
R1: 33R; R_0402_1005Metric; LCSC C25105
U1: 74AHCT1G125; SOT-23-5; LCSC C7484

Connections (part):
+5V: C1.1, C2.1, C3.1, C4.1, C5.1, C6.1, C7.1, C8.1, C9.1, C10.1, C11.1, C12.1, C13.1, C14.1, C15.1, C16.1, C17.1, C18.1, C19.1, C20.1, C21.1, C22.1, C23.1, C24.1, C25.1, C26.1, C27.1, C28.1, C29.1, C30.1, C31.1, C32.1, C33.1, C34.1, C35.1, C36.1, C37.1, C38.1, C39.1, C40.1, C41.1, C42.1, C43.1, C44.1, C45.1, C46.1, C47.1, C48.1, C49.1, C50.1, C51.1, C52.1, C53.1, C54.1, C55.1, C56.1, C57.1, C58.1, C59.1, C60.1, C61.1, C62.1, C63.1, C64.1, C65.1, C66.1, C67.1, C68.1, C69.1, C70.1, C71.1, C72.1, C73.1, C74.1, C75.1, C76.1, C77.1, C78.1, C79.1, C80.1, C81.1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
/D000: D1.4 (DIN), R1.1
/D001: D1.2 (DOUT), D2.4 (DIN)
/D002: D2.2 (DOUT), D3.4 (DIN)
/D003: D3.2 (DOUT), D4.4 (DIN)
/D004: D4.2 (DOUT), D5.4 (DIN)
/D005: D5.2 (DOUT), D6.4 (DIN)
/D006: D6.2 (DOUT), D7.4 (DIN)
/D007: D7.2 (DOUT), D8.4 (DIN)
/D008: D8.2 (DOUT), D9.4 (DIN)
/D009: D9.2 (DOUT), D10.4 (DIN)
/D010: D10.2 (DOUT), D11.4 (DIN)
/D011: D11.2 (DOUT), D12.4 (DIN)
/D012: D12.2 (DOUT), D13.4 (DIN)
/D013: D13.2 (DOUT), D14.4 (DIN)
/D014: D14.2 (DOUT), D15.4 (DIN)
/D015: D15.2 (DOUT), D16.4 (DIN)
/D016: D16.2 (DOUT), D17.4 (DIN)
/D017: D17.2 (DOUT), D18.4 (DIN)
/D018: D18.2 (DOUT), D19.4 (DIN)
/D019: D19.2 (DOUT), D20.4 (DIN)
/D020: D20.2 (DOUT), D21.4 (DIN)
/D021: D21.2 (DOUT), D22.4 (DIN)
/D022: D22.2 (DOUT), D23.4 (DIN)
/D023: D23.2 (DOUT), D24.4 (DIN)
/D024: D24.2 (DOUT), D25.4 (DIN)
/D025: D25.2 (DOUT), D26.4 (DIN)
/D026: D26.2 (DOUT), D27.4 (DIN)
/D027: D27.2 (DOUT), D28.4 (DIN)
/D028: D28.2 (DOUT), D29.4 (DIN)
/D029: D29.2 (DOUT), D30.4 (DIN)
/D030: D30.2 (DOUT), D31.4 (DIN)
/D031: D31.2 (DOUT), D32.4 (DIN)
/D032: D32.2 (DOUT), D33.4 (DIN)
/D033: D33.2 (DOUT), D34.4 (DIN)
/D034: D34.2 (DOUT), D35.4 (DIN)
/D035: D35.2 (DOUT), D36.4 (DIN)
/D036: D36.2 (DOUT), D37.4 (DIN)
/D037: D37.2 (DOUT), D38.4 (DIN)
/D038: D38.2 (DOUT), D39.4 (DIN)
/D039: D39.2 (DOUT), D40.4 (DIN)
/D040: D40.2 (DOUT), D41.4 (DIN)
/D041: D41.2 (DOUT), D42.4 (DIN)
/D042: D42.2 (DOUT), D43.4 (DIN)
/D043: D43.2 (DOUT), D44.4 (DIN)
/D044: D44.2 (DOUT), D45.4 (DIN)
/D045: D45.2 (DOUT), D46.4 (DIN)
/D046: D46.2 (DOUT), D47.4 (DIN)
/D047: D47.2 (DOUT), D48.4 (DIN)
/D048: D48.2 (DOUT), D49.4 (DIN)
/D049: D49.2 (DOUT), D50.4 (DIN)
/D050: D50.2 (DOUT), D51.4 (DIN)
/D051: D51.2 (DOUT), D52.4 (DIN)
/D052: D52.2 (DOUT), D53.4 (DIN)
/D053: D53.2 (DOUT), D54.4 (DIN)
/D054: D54.2 (DOUT), D55.4 (DIN)
/D055: D55.2 (DOUT), D56.4 (DIN)
/D056: D56.2 (DOUT), D57.4 (DIN)
/D057: D57.2 (DOUT), D58.4 (DIN)
/D058: D58.2 (DOUT), D59.4 (DIN)
/D059: D59.2 (DOUT), D60.4 (DIN)
/D060: D60.2 (DOUT), D61.4 (DIN)
/D061: D61.2 (DOUT), D62.4 (DIN)
/D062: D62.2 (DOUT), D63.4 (DIN)
/D063: D63.2 (DOUT), D64.4 (DIN)
/D064: D64.2 (DOUT), D65.4 (DIN)
/D065: D65.2 (DOUT), D66.4 (DIN)
/D066: D66.2 (DOUT), D67.4 (DIN)
/D067: D67.2 (DOUT), D68.4 (DIN)
/D068: D68.2 (DOUT), D69.4 (DIN)
/D069: D69.2 (DOUT), D70.4 (DIN)
/D070: D70.2 (DOUT), D71.4 (DIN)
/D071: D71.2 (DOUT), D72.4 (DIN)
/D072: D72.2 (DOUT), D73.4 (DIN)
/D073: D73.2 (DOUT), D74.4 (DIN)
/D074: D74.2 (DOUT), D75.4 (DIN)
/D075: D75.2 (DOUT), D76.4 (DIN)
/D076: D76.2 (DOUT), D77.4 (DIN)
/D077: D77.2 (DOUT), D78.4 (DIN)
/D078: D78.2 (DOUT), D79.4 (DIN)
/D079: D79.2 (DOUT), D80.4 (DIN)
/D080: D80.2 (DOUT), D81.4 (DIN)
/D081: D81.2 (DOUT), D82.4 (DIN)
/D082: D82.2 (DOUT), D83.4 (DIN)
/D083: D83.2 (DOUT), D84.4 (DIN)
/D084: D84.2 (DOUT), D85.4 (DIN)
/D085: D85.2 (DOUT), D86.4 (DIN)
/D086: D86.2 (DOUT), D87.4 (DIN)
/D087: D87.2 (DOUT), D88.4 (DIN)
/D088: D88.2 (DOUT), D89.4 (DIN)
/D089: D89.2 (DOUT), D90.4 (DIN)
/D090: D90.2 (DOUT), D91.4 (DIN)
/D091: D91.2 (DOUT), D92.4 (DIN)
/D092: D92.2 (DOUT), D93.4 (DIN)
/D093: D93.2 (DOUT), D94.4 (DIN)
/D094: D94.2 (DOUT), D95.4 (DIN)
/D095: D95.2 (DOUT), D96.4 (DIN)
/D096: D96.2 (DOUT), D97.4 (DIN)
/D097: D97.2 (DOUT), D98.4 (DIN)
/D098: D98.2 (DOUT), D99.4 (DIN)
/D099: D99.2 (DOUT), D100.4 (DIN)
/D100: D100.2 (DOUT), D101.4 (DIN)
/D101: D101.2 (DOUT), D102.4 (DIN)
/D102: D102.2 (DOUT), D103.4 (DIN)
/D103: D103.2 (DOUT), D104.4 (DIN)
/D104: D104.2 (DOUT), D105.4 (DIN)
/D105: D105.2 (DOUT), D106.4 (DIN)
/D106: D106.2 (DOUT), D107.4 (DIN)
/D107: D107.2 (DOUT), D108.4 (DIN)
/D108: D108.2 (DOUT), D109.4 (DIN)
/D109: D109.2 (DOUT), D110.4 (DIN)
/D110: D110.2 (DOUT), D111.4 (DIN)
/D111: D111.2 (DOUT), D112.4 (DIN)
/D112: D112.2 (DOUT), D113.4 (DIN)
/D113: D113.2 (DOUT), D114.4 (DIN)
/D114: D114.2 (DOUT), D115.4 (DIN)
/D115: D115.2 (DOUT), D116.4 (DIN)
/D116: D116.2 (DOUT), D117.4 (DIN)
/D117: D117.2 (DOUT), D118.4 (DIN)
/D118: D118.2 (DOUT), D119.4 (DIN)
/D119: D119.2 (DOUT), D120.4 (DIN)
/D120: D120.2 (DOUT), D121.4 (DIN)
/D121: D121.2 (DOUT), D122.4 (DIN)
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
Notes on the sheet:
WS2812B Matrix 16x16, Raster 10 mm, 2 Lagen - Datenkette D1 -> D256 als Serpentine, Anordnung wie auf der Platine
Eingang: 3,3V-Daten -> Pegelwandler -> D1 | Ausgang D256 -> J3 | Einspeisung +5V/GND (Unterseite)
